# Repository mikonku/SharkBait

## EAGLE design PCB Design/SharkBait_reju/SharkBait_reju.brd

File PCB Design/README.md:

# SharkBait

SharkBait is an Atmega2560 minimum system development project, complete with its RTC circuits and data loggers. And equipped with two connectors for interfacing with sensors.

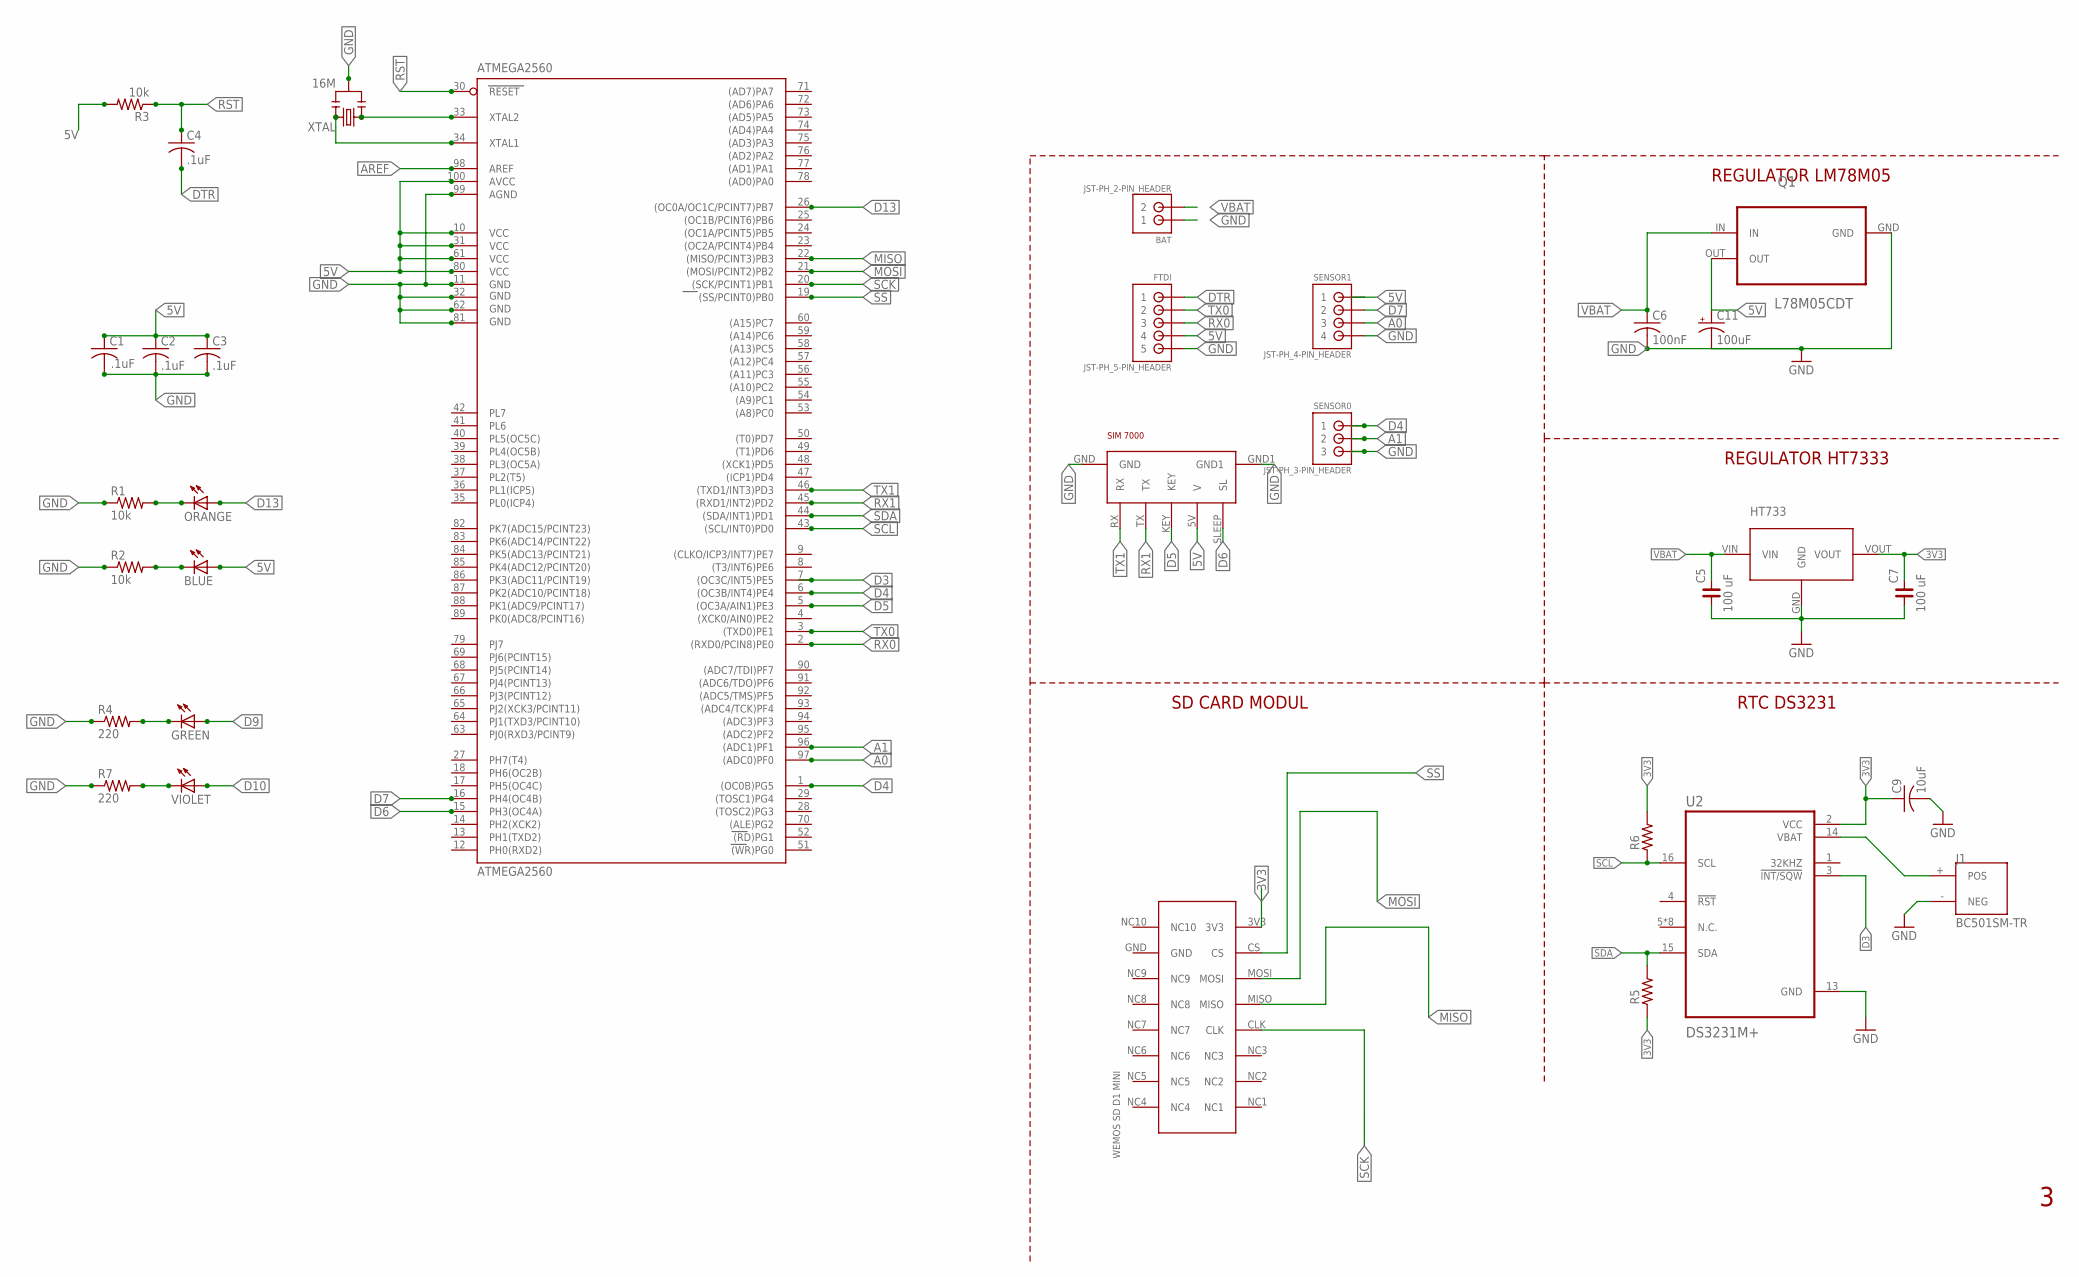
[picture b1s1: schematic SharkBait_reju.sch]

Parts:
ATMEGA2560: ATMEGA2560; TQFP100
BAT: JST-PH_2-PIN_HEADER; JST_B2B-PH_HEADER
BLUE: L; SMD-0805-LED
C1: CAPACITOR-SMD-0805; SMD-0805
C2, C3, C4: .1uF; SMD-0805
C5, C7: 100 uF; C0805
C6: 100nF; C1206
C9: 10uF; SMD-0805
C11: 100uF; PANASONIC_D
FTDI: JST-PH_5-PIN_HEADER; JST_B5B-PH_HEADER
GREEN: L; SMD-0805-LED
HT733: HT7333; SOT89
J1: BC501SM-TR; MPD_BC501SM-TR
ORANGE: L; SMD-0805-LED
Q1: L78M05CDT; TO225P972X240-3N
R1, R2, R3: 10k; SMD-0805
R4, R7: 220; SMD-0805
R5, R6: R_0805; R0805
SENSOR0: JST-PH_3-PIN_HEADER; JST_B3B-PH_HEADER
SENSOR1: JST-PH_4-PIN_HEADER; JST_B4B-PH_HEADER
U2: DS3231M+; SOIC127P1032X265-16N
U$1: WEMOS_SD_D1_MINI
U$2: SIM7000; SIM_7000
VIOLET: L; SMD-0805-LED
XTAL: 16M; RESONATOR

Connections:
3V3: C7.2, C9.1, HT733.VOUT, R5.1, R6.2, U2.2 (VCC), U$1.3V3
5V: ATMEGA2560.10 (VCC), ATMEGA2560.31 (VCC1), ATMEGA2560.61 (VCC2), ATMEGA2560.80 (VCC3), ATMEGA2560.100 (AVCC), BLUE.1 (A), C1.1, C2.1, C3.1, C11.+, FTDI.P4 (4), Q1.OUT, R3.2, SENSOR1.P1 (1), U$2.5V (V)
A0: ATMEGA2560.97 ((ADC0)PF0), SENSOR1.P3 (3)
A1: ATMEGA2560.96 ((ADC1)PF1), SENSOR0.P2 (2)
AREF: ATMEGA2560.98 (AREF)
D3: ATMEGA2560.7 ((OC3C/INT5)PE5), U2.3 (!INT/SQW)
D4: ATMEGA2560.1 ((OC0B)PG5), ATMEGA2560.6 ((OC3B/INT4)PE4), SENSOR0.P1 (1)
D5: ATMEGA2560.5 ((OC3A/AIN1)PE3), U$2.KEY
D6: ATMEGA2560.15 (PH3(OC4A)), U$2.SLEEP (SL)
D7: ATMEGA2560.16 (PH4(OC4B)), SENSOR1.P2 (2)
D9: GREEN.1 (A)
D10: VIOLET.1 (A)
D13: ATMEGA2560.26 ((OC0A/OC1C/PCINT7)PB7), ORANGE.1 (A)
DTR: C4.2, FTDI.P1 (1)
GND: ATMEGA2560.11 (GND), ATMEGA2560.32 (GND1), ATMEGA2560.62 (GND2), ATMEGA2560.81 (GND3), ATMEGA2560.99 (AGND), BAT.P1 (1), C1.2, C2.2, C3.2, C5.1, C6.2, C7.1, C9.2, C11.-, FTDI.P5 (5), HT733.GND, J1.- (NEG), Q1.GND, R1.1, R2.1, R4.1, R7.1, SENSOR0.P3 (3), SENSOR1.P4 (4), U2.13 (GND), U$2.GND, U$2.GND1, XTAL.2
MISO: ATMEGA2560.22 ((MISO/PCINT3)PB3), U$1.MISO
MOSI: ATMEGA2560.21 ((MOSI/PCINT2)PB2), U$1.MOSI
unnamed: J1.+ (POS), U2.14 (VBAT)
unnamed: GREEN.2 (C), R4.2
unnamed: R7.2, VIOLET.2 (C)
unnamed: ATMEGA2560.34 (XTAL1), XTAL.3
unnamed: ATMEGA2560.33 (XTAL2), XTAL.1
unnamed: ORANGE.2 (C), R1.2
unnamed: BLUE.2 (C), R2.2
RST: ATMEGA2560.30 (RESET), C4.1, R3.1
RX0: ATMEGA2560.2 ((RXD0/PCIN8)PE0), FTDI.P3 (3)
RX1: ATMEGA2560.45 ((RXD1/INT2)PD2), U$2.TX
SCK: ATMEGA2560.20 ((SCK/PCINT1)PB1), U$1.CLK
SCL: ATMEGA2560.43 ((SCL/INT0)PD0), R6.1, U2.16 (SCL)
SDA: ATMEGA2560.44 ((SDA/INT1)PD1), R5.2, U2.15 (SDA)
SS: ATMEGA2560.19 ((SS/PCINT0)PB0), U$1.CS
TX0: ATMEGA2560.3 ((TXD0)PE1), FTDI.P2 (2)
TX1: ATMEGA2560.46 ((TXD1/INT3)PD3), U$2.RX
VBAT: BAT.P2 (2), C5.2, C6.1, HT733.VIN, Q1.IN

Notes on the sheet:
.1uF
RTC DS3231
REGULATOR HT7333
REGULATOR LM78M05
SD CARD MODUL

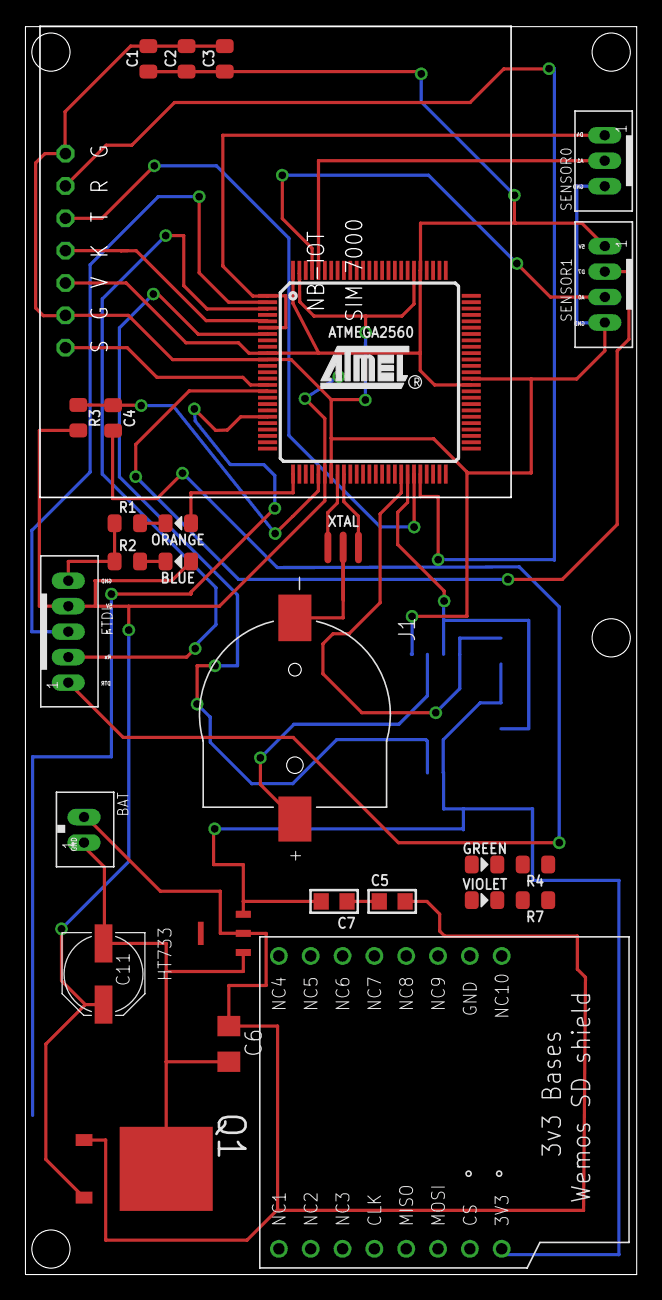
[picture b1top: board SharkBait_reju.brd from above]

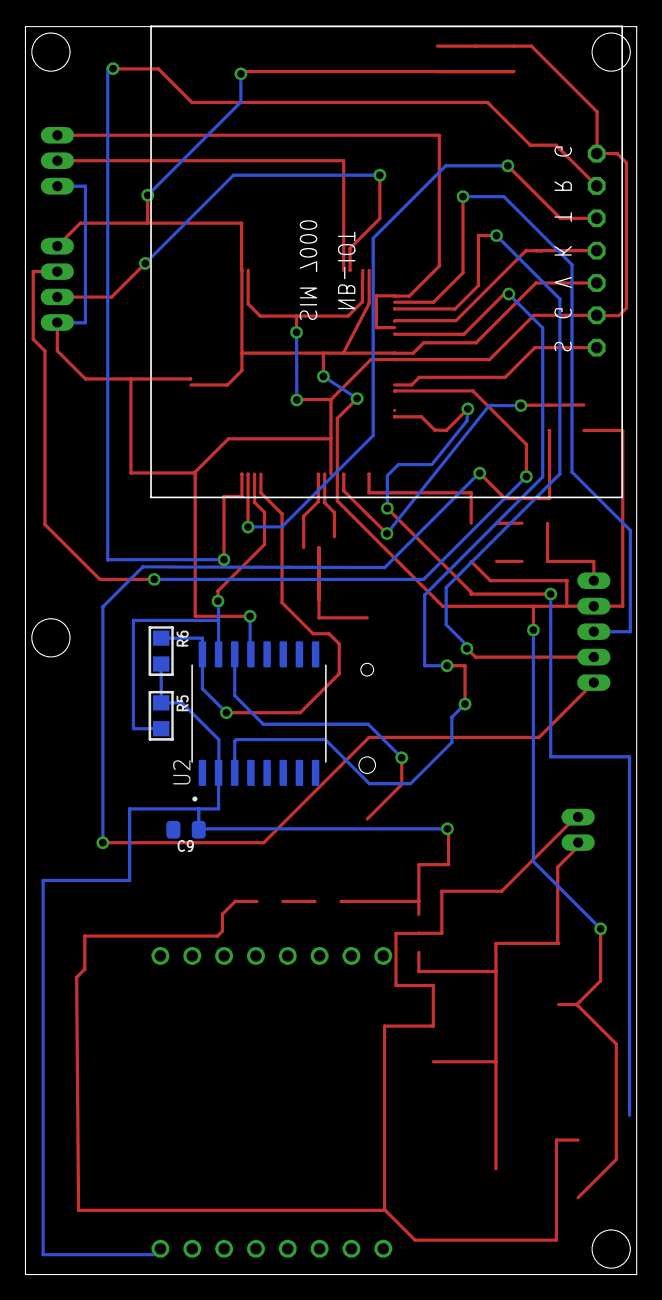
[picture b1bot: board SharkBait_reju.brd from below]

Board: 2 copper layers, 48.0 x 98.0 mm, 32 parts (4 on the bottom side), 31 nets.

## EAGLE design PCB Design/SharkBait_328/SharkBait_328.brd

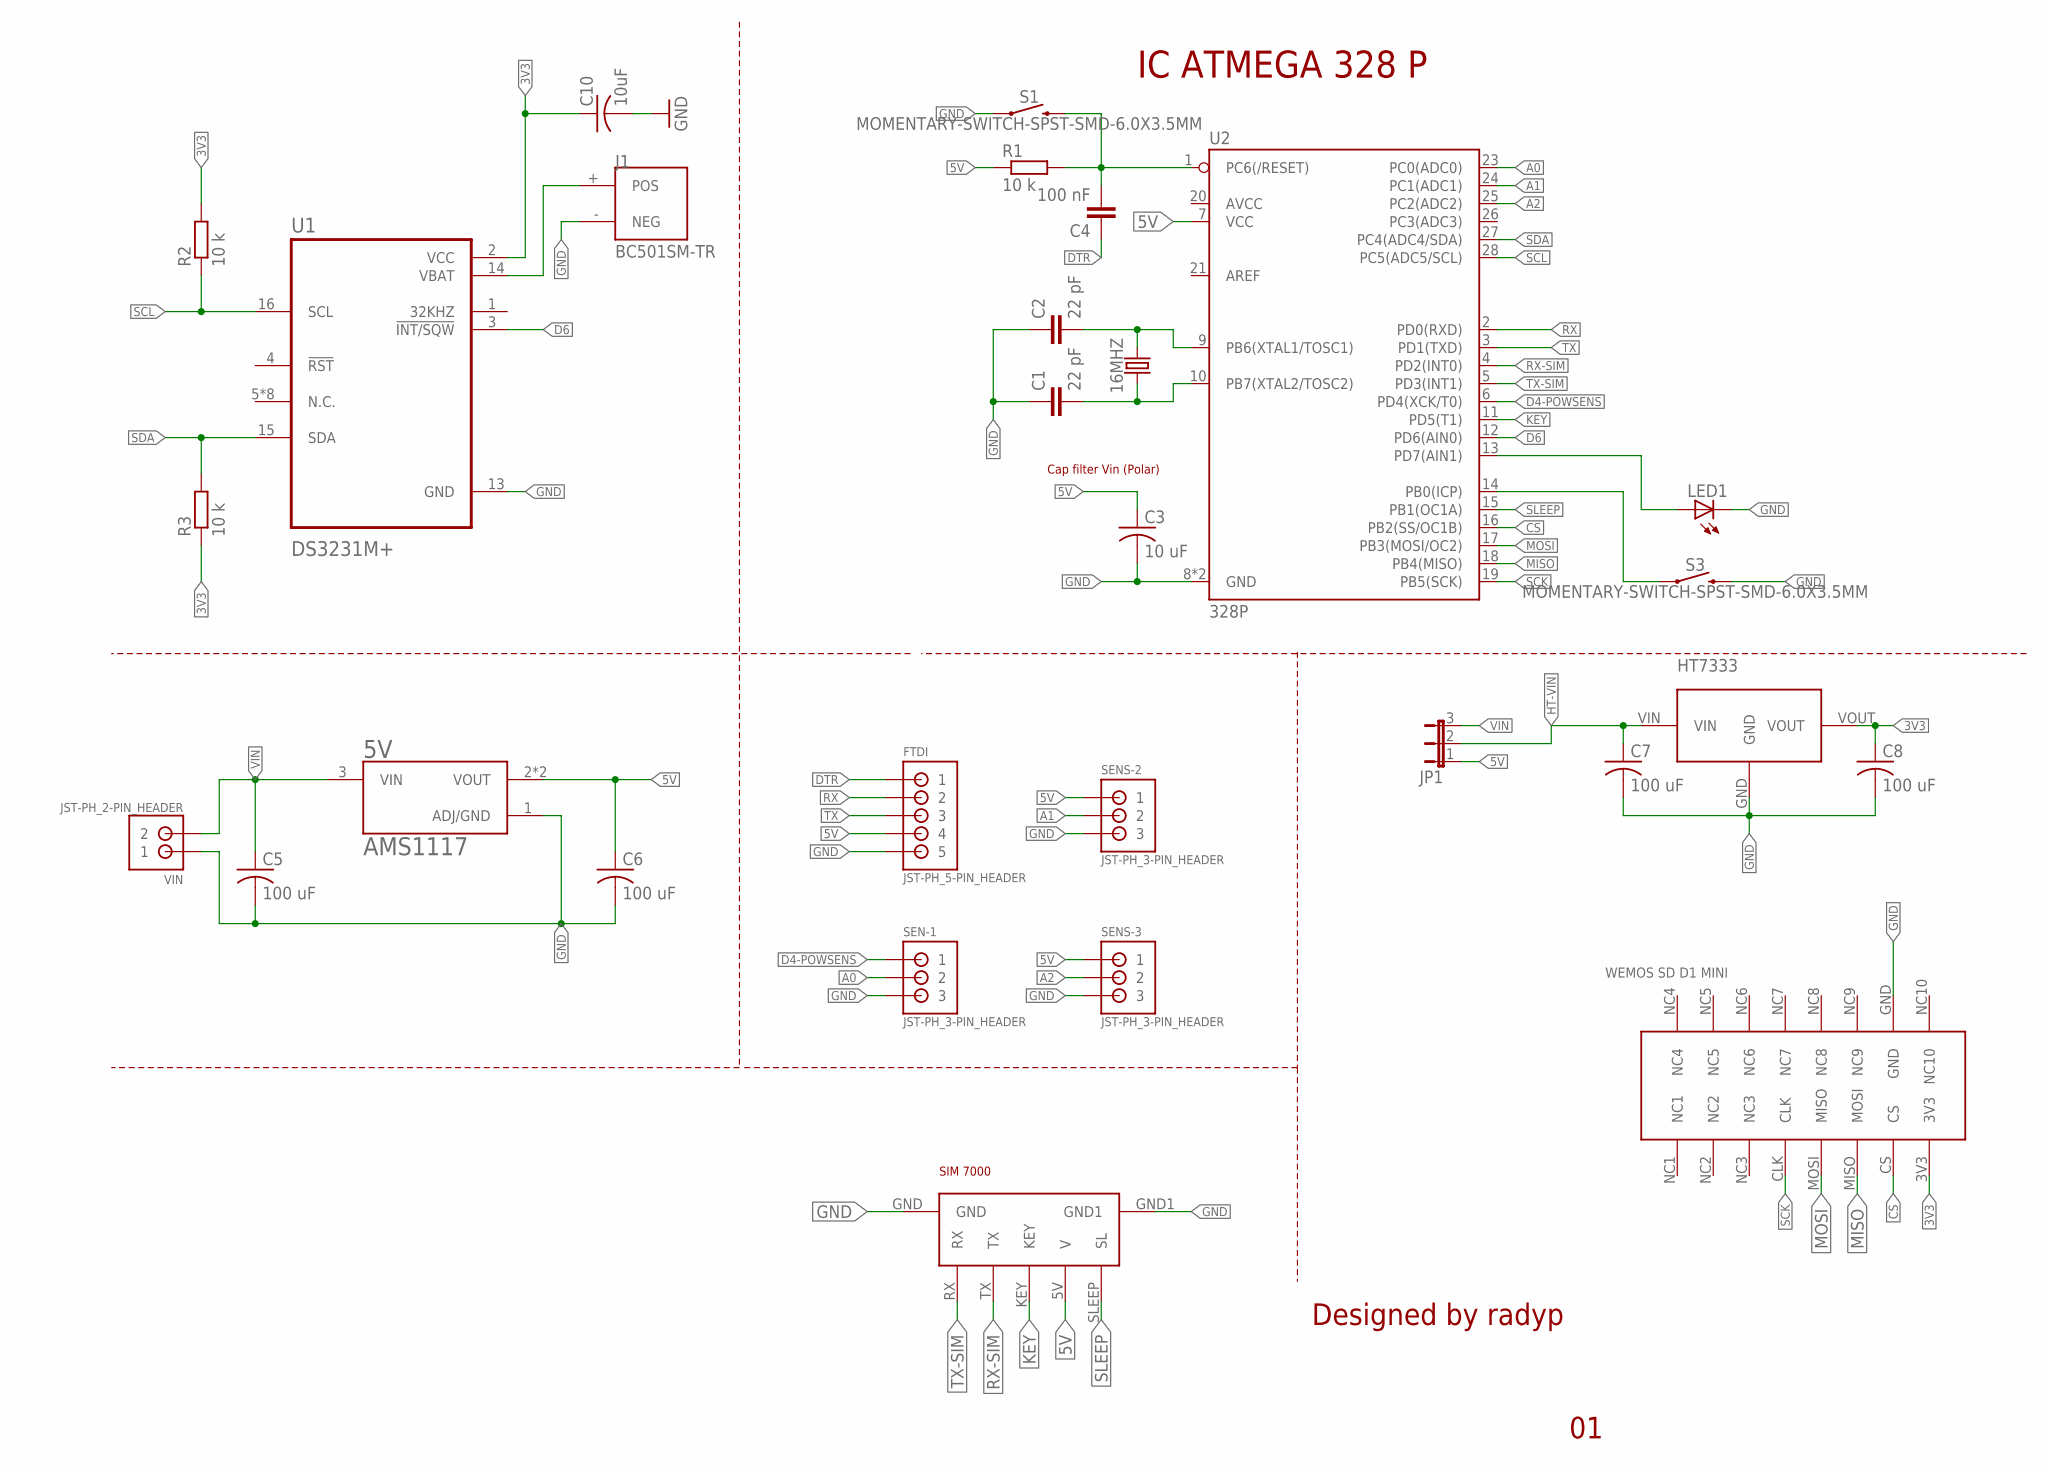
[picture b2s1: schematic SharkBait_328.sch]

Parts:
5V: AMS1117; SOT229P700X180-4N
16MHZ: CRYSTALPTH-HC49US; HC49US
C1, C2: 22 pF; C0805
C3: 10 uF; C1206
C4: 100 nF; C0805
C5, C6, C7, C8: 100 uF; C1206
C10: 10uF; SMD-0805
FTDI: JST-PH_5-PIN_HEADER; JST_B5B-PH_HEADER
HT7333: HT7333; SOT89
J1: BC501SM-TR; MPD_BC501SM-TR
JP1: JP2E; JP2
LED1: LEDCHIP-LED0805; CHIP-LED0805
R1, R2, R3: 10 k; M0805
S1, S3: MOMENTARY-SWITCH-SPST-SMD-6.0X3.5MM; TACTILE_SWITCH_SMD_6.0X3.5MM
SEN-1: JST-PH_3-PIN_HEADER; JST_B3B-PH_HEADER
SENS-2, SENS-3: JST-PH_3-PIN_HEADER; JST_B3B-PH_HEADER
U1: DS3231M+; SOIC127P1032X265-16N
U2: 328P; DIP28
U$1: WEMOS_SD_D1_MINI
U$2: SIM7000; SIM_7000
VIN: JST-PH_2-PIN_HEADER; JST_B2B-PH_HEADER

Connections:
3V3: C8.1, C10.1, HT7333.VOUT, R2.2, R3.1, U1.2 (VCC), U$1.3V3
5V: 5V.2 (VOUT), 5V.4 (VOUT), C3.1, C6.1, FTDI.P4 (4), JP1.1, R1.1, SENS-2.P1 (1), SENS-3.P1 (1), U2.7 (VCC), U$2.5V (V)
A0: SEN-1.P2 (2), U2.23 (PC0(ADC0))
A1: SENS-2.P2 (2), U2.24 (PC1(ADC1))
A2: SENS-3.P2 (2), U2.25 (PC2(ADC2))
CS: U2.16 (PB2(SS/OC1B)), U$1.CS
D4-POWSENS: SEN-1.P1 (1), U2.6 (PD4(XCK/T0))
D6: U1.3 (!INT/SQW), U2.12 (PD6(AIN0))
DTR: C4.1, FTDI.P1 (1)
GND: 5V.1 (ADJ/GND), C1.1, C2.1, C3.2, C5.2, C6.2, C7.2, C8.2, C10.2, FTDI.P5 (5), HT7333.GND, J1.- (NEG), LED1.C, S1.1, S3.2, SEN-1.P3 (3), SENS-2.P3 (3), SENS-3.P3 (3), U1.13 (GND), U2.8 (GND), U2.22 (GND), U$1.GND, U$2.GND, U$2.GND1, VIN.P1 (1)
HT-VIN: C7.1, HT7333.VIN, JP1.2
KEY: U2.11 (PD5(T1)), U$2.KEY
MISO: U2.18 (PB4(MISO)), U$1.MISO (MOSI)
MOSI: U2.17 (PB3(MOSI/OC2)), U$1.MOSI (MISO)
unnamed: 16MHZ.2, C2.2, U2.9 (PB6(XTAL1/TOSC1))
unnamed: 16MHZ.1, C1.2, U2.10 (PB7(XTAL2/TOSC2))
unnamed: J1.+ (POS), U1.14 (VBAT)
unnamed: LED1.A, U2.13 (PD7(AIN1))
unnamed: S3.1, U2.14 (PB0(ICP))
unnamed: C4.2, R1.2, S1.2, U2.1 (PC6(/RESET))
RX: FTDI.P2 (2), U2.2 (PD0(RXD))
RX-SIM: U2.4 (PD2(INT0)), U$2.TX
SCK: U2.19 (PB5(SCK)), U$1.CLK
SCL: R2.1, U1.16 (SCL), U2.28 (PC5(ADC5/SCL))
SDA: R3.2, U1.15 (SDA), U2.27 (PC4(ADC4/SDA))
SLEEP: U2.15 (PB1(OC1A)), U$2.SLEEP (SL)
TX: FTDI.P3 (3), U2.3 (PD1(TXD))
TX-SIM: U2.5 (PD3(INT1)), U$2.RX
VIN: 5V.3 (VIN), C5.1, JP1.3, VIN.P2 (2)

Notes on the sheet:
Designed by radyp
IC ATMEGA 328 P
Cap filter Vin (Polar)

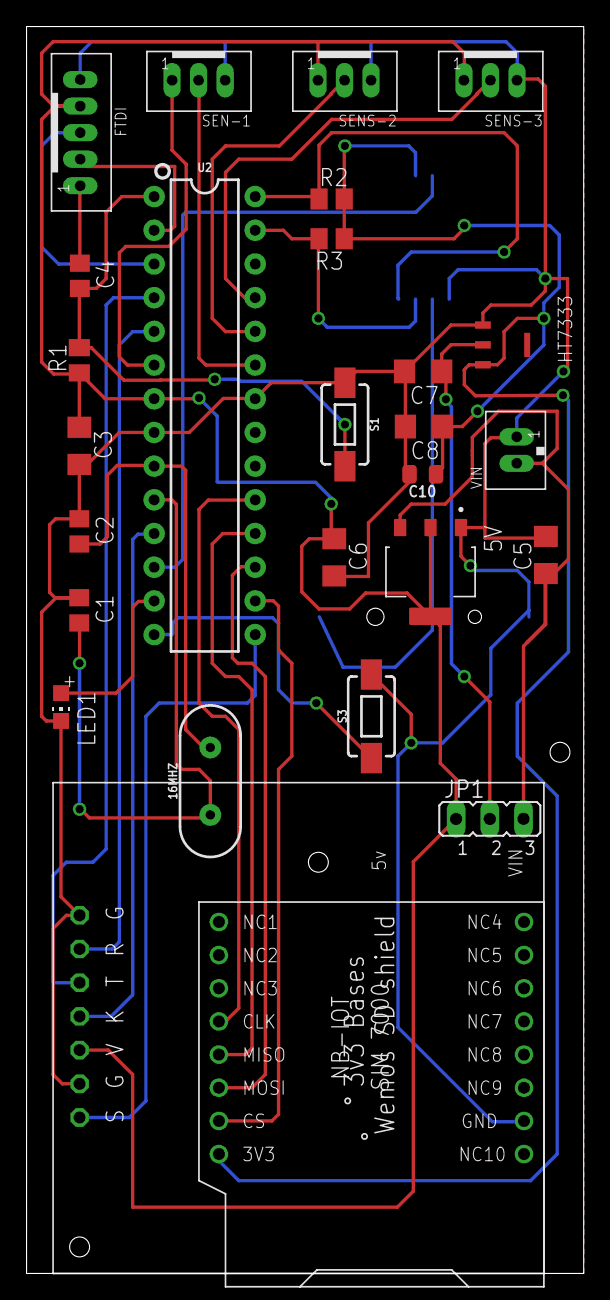
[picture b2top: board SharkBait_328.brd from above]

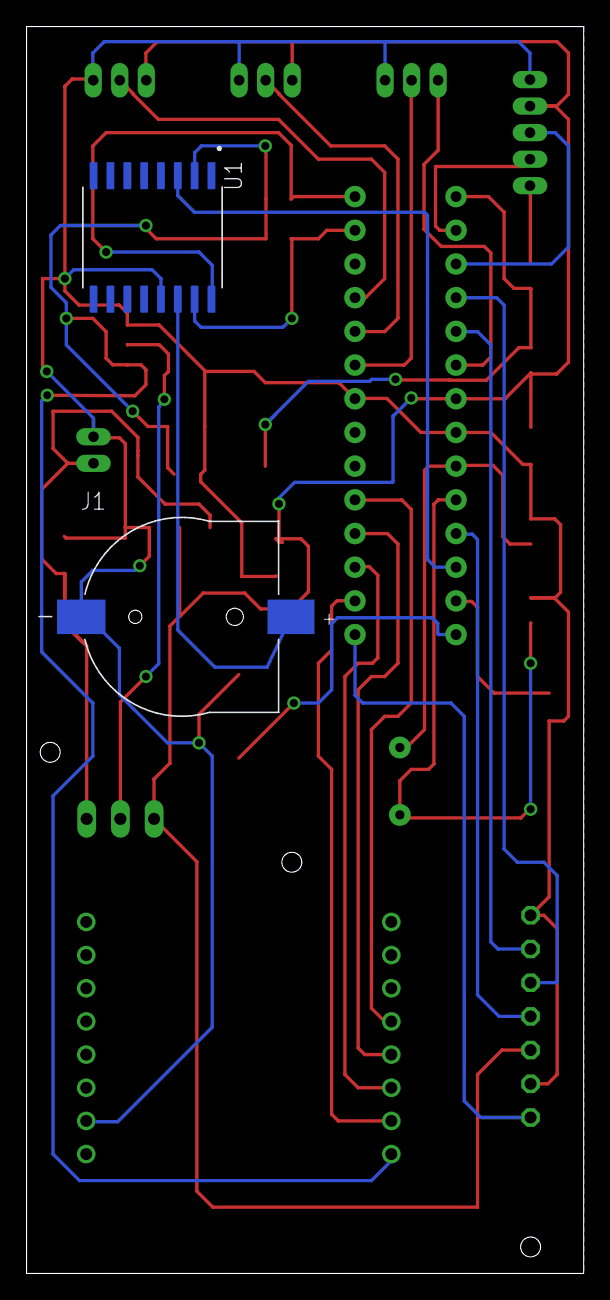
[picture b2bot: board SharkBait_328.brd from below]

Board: 2 copper layers, 42.0 x 94.0 mm, 29 parts (2 on the bottom side), 29 nets.

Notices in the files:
parts and their libraries:
SparkFun-IC-Microcontroller: Licensing: Creative Commons ShareAlike 4.0 International - https://creativecommons.org/licenses/by-sa/4.0
rc-master-smd: Copyright (C) 2007, Bob Starr
